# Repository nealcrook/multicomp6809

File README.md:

---
DOCUMENTATION: For instructions and other documentation for these files, refer to the Wiki (use the link at the top of the page). You might not see the link if you are using a mobile device -- you may need to select "desktop version"
---

I always wanted a 6809 machine. I still have the A4 notebook where I sketched out design ideas. However, I never simultaneously had the time and money to build one from scratch (even though I have accumulated all of the parts in my junk box over the years).

When I saw this http://searle.hostei.com/grant/Multicomp/index.html I realised I could satisfy my yearning without too much soldering.

I decided that I would run Brad Rodriguez's Camelforth on it. Before I did that I resussitated a 6809 emulator and added crude support first for Brad's "scroungmaster" machine and then for the 6809 multicomp machine. That emulator is https://github.com/nealcrook/exec09.

Camelforth is currently running on real hardware. Using a hardware bank-switching unit on multicomp Camelforth can also act as boot loader for Grant's port of Microsoft ROM BASIC and for the N8VEM port of Dave Dunfield's CUBIX and for my ports of FLEX, NitrOS-9, BUGGY and FUZIX. All of this also runs on exec09.

This repository is a venue for sharing the hardware and software that I have used on my multicomp.

For detail on how to use any of this stuff, click on the "wiki" button on the right.

More on CamelForth here:
https://launchpad.net/camelforth
http://www.camelforth.com/
http://www.bradrodriguez.com/papers/index.html

Approximate WIKI Change Log:

03Feb2016 Rework FLEX stuff to add more detail and make it clearer

05Feb2016 Rework CUBIX stuff to describe new single-step boot. Remove references to obsolete SDINIT.

12Feb2016 New BUGGY source code - single step now works. Expanded WIKI pages on CamelForth to add some links on tutorials. New versions of TERMINAL and UART VHDL to add functional reset of input FIFOs to avoid some start-up problems.

09Aug2018 Tidy-up pass - adding a few misisng files and scripts and generally tidying things up. In particular, clean up the build process for the 6809 ROM BASIC and add some images for simulation debug.

06Mar2019 Reorganisation to try to provided consistent descriptions for each operating environment: the original material  evolved over time as I ported successive bits of code and it shows (too much) in places.

24May2020 WIKI was a mix of creole and markdown. I am gradually migrating all the pages to markdown, making various small updates on the way. Expand the pages on camelforth to describe how to build it at a different start address.

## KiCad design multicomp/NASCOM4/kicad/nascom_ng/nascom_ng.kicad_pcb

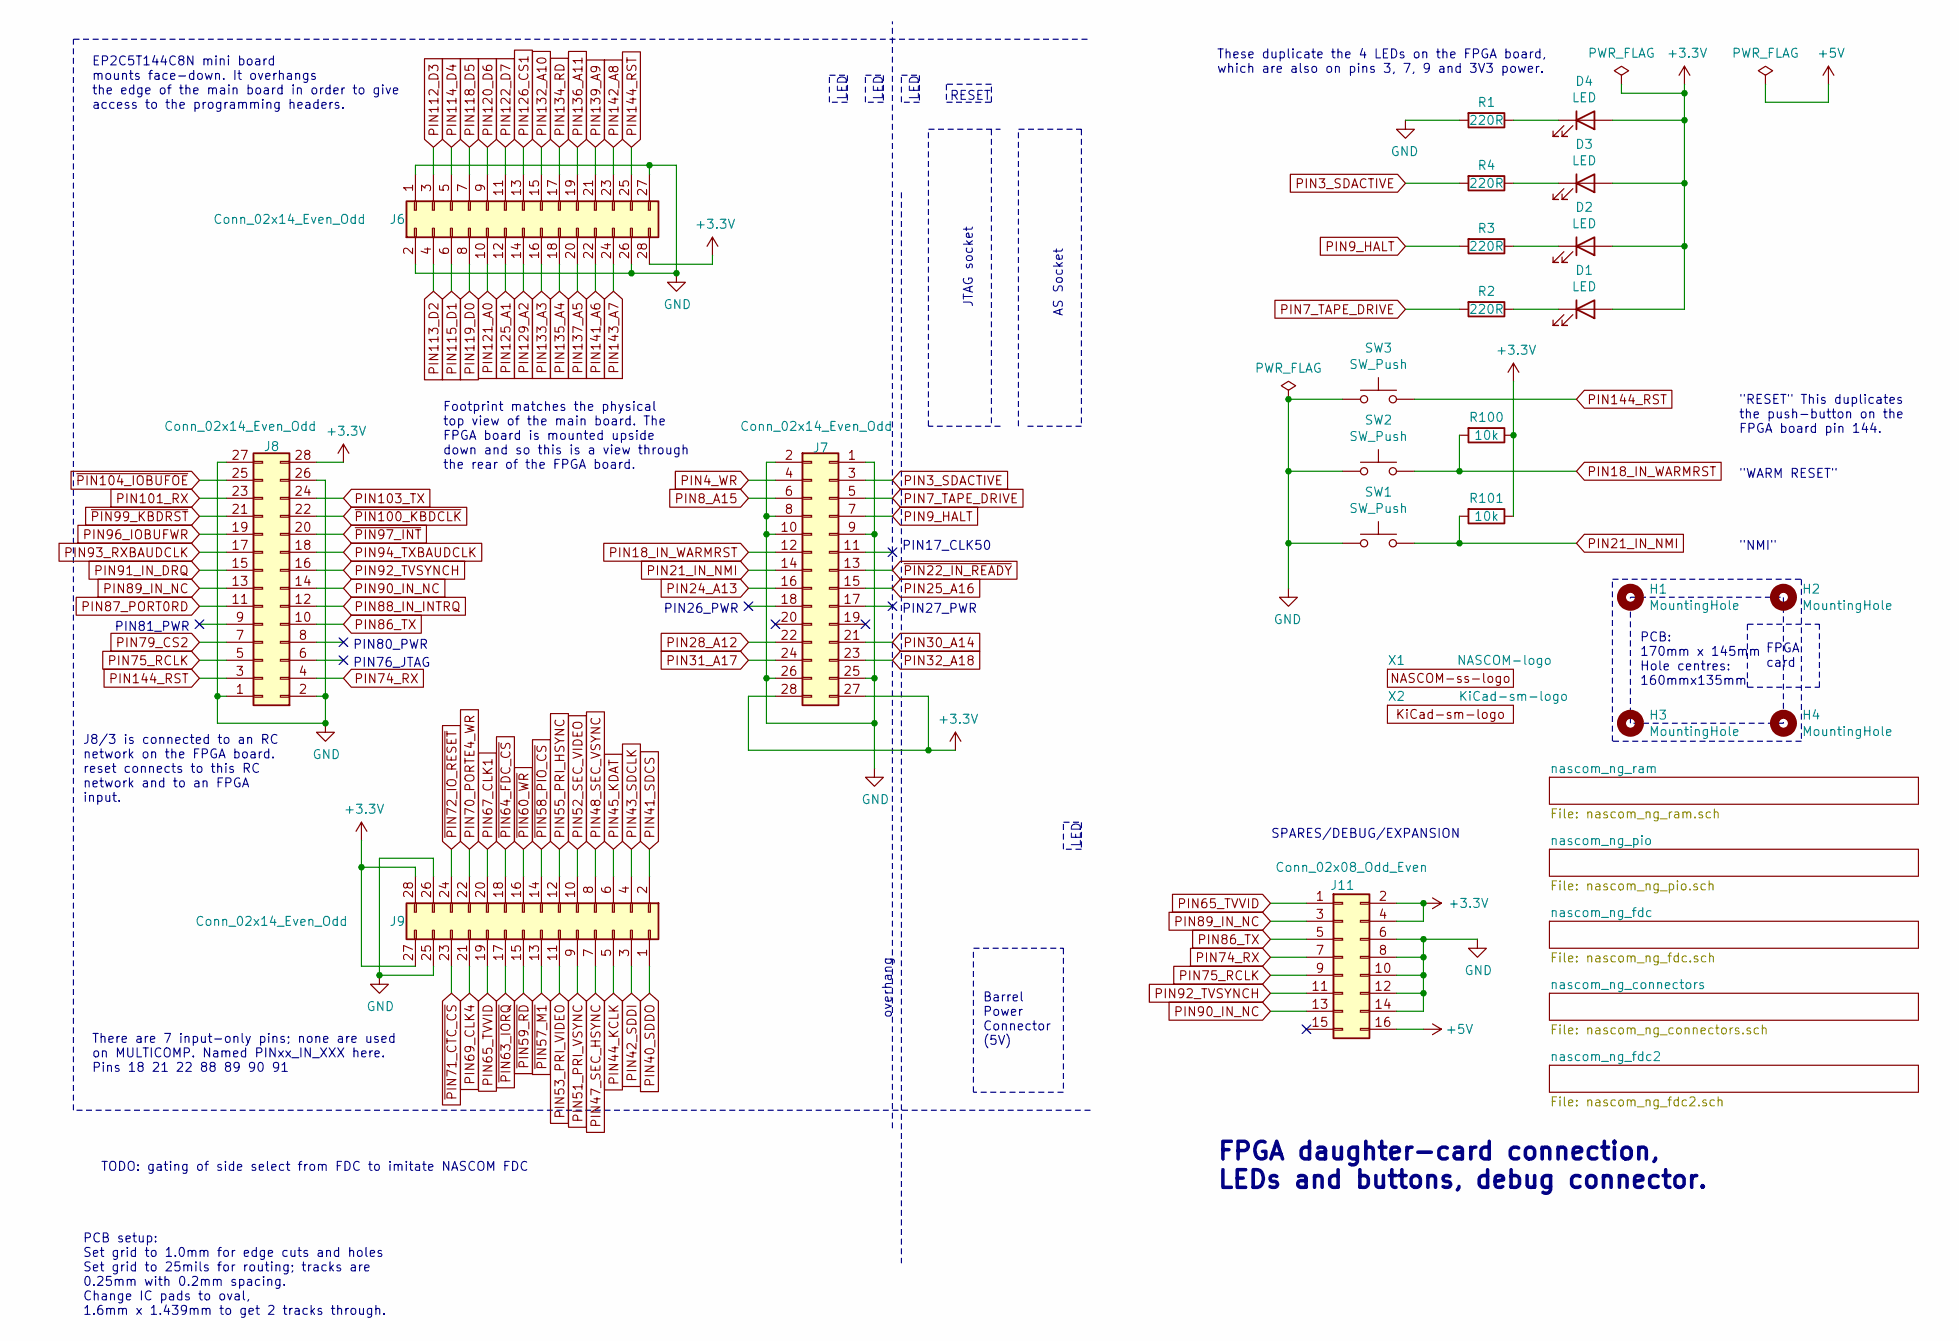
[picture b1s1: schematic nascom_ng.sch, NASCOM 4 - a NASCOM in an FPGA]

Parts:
D1, D2, D3, D4: LED; LED_D5.0mm
H1, H2, H3, H4: MountingHole; MountingHole_3.2mm_M3
J6, J7, J8, J9: Conn_02x14_Even_Odd; PinSocket_2x14_P2.54mm_Vertical
J11: Conn_02x08_Odd_Even; IDC-Header_2x08_P2.54mm_Vertical
R1, R2, R3, R4: 220R; R_Axial_DIN0204_L3.6mm_D1.6mm_P7.62mm_Horizontal
R100, R101: 10k; R_Axial_DIN0204_L3.6mm_D1.6mm_P7.62mm_Horizontal
SW1, SW2, SW3: SW_Push; MOMENTARY_TACTILE_RT_ANGLE
X1: NASCOM-logo; nascom_logo_tiny
X2: KiCad-sm-logo; KiCad-Logo_5mm_SolderMask

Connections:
+5V: J11.16; also elsewhere on the board
GND: J6.1, J6.2, J6.26, J6.27, J7.1, J7.2, J7.8, J7.9, J7.10, J7.25, J7.26, J8.1, J8.2, J8.26, J8.27, J9.25, J9.26, J11.6, J11.8, J11.10, J11.12, J11.14, R1.2, SW1.1, SW2.1, SW3.1; also elsewhere on the board
unnamed: D1.1 (K), R2.1
unnamed: D2.1 (K), R3.1
unnamed: D3.1 (K), R4.1
unnamed: D4.1 (K), R1.1
PIN3_SDACTIVE: J7.3, R4.2
PIN4_WR: J7.4; also elsewhere on the board
PIN7_TAPE_DRIVE: J7.5, R2.2; also elsewhere on the board
PIN8_A15: J7.6; also elsewhere on the board
PIN9_HALT: J7.7, R3.2
PIN18_IN_WARMRST: J7.12, R100.2, SW2.2
PIN21_IN_NMI: J7.14, R101.2, SW1.2; also elsewhere on the board
PIN24_A13: J7.16; also elsewhere on the board
PIN25_A16: J7.15; also elsewhere on the board
PIN28_A12: J7.22; also elsewhere on the board
PIN30_A14: J7.21; also elsewhere on the board
PIN31_A17: J7.24; also elsewhere on the board
PIN32_A18: J7.23; also elsewhere on the board
PIN40_SDDO: J9.1; also elsewhere on the board
PIN41_SDCS: J9.2; also elsewhere on the board
PIN42_SDDI: J9.3; also elsewhere on the board
PIN43_SDCLK: J9.4; also elsewhere on the board
PIN44_KCLK: J9.5; also elsewhere on the board
PIN45_KDAT: J9.6; also elsewhere on the board
PIN47_SEC_HSYNC: J9.7; also elsewhere on the board
PIN48_SEC_VSYNC: J9.8; also elsewhere on the board
PIN51_PRI_VSYNC: J9.9; also elsewhere on the board
PIN52_SEC_VIDEO: J9.10; also elsewhere on the board
PIN53_PRI_VIDEO: J9.11; also elsewhere on the board
PIN55_PRI_HSYNC: J9.12; also elsewhere on the board
PIN65_TVVID: J9.19, J11.1
PIN67_CLK1: J9.20; also elsewhere on the board
PIN69_CLK4: J9.21; also elsewhere on the board
PIN70_PORTE4_WR: J9.22; also elsewhere on the board
PIN74_RX: J8.4, J11.7
PIN75_RCLK: J8.5, J11.9
PIN79_CS2: J8.7; also elsewhere on the board
PIN86_TX: J8.10, J11.5
PIN87_PORT0RD: J8.11; also elsewhere on the board
PIN88_IN_INTRQ: J8.12; also elsewhere on the board
PIN89_IN_NC: J8.13, J11.3
PIN90_IN_NC: J8.14, J11.13
PIN91_IN_DRQ: J8.15; also elsewhere on the board
PIN92_TVSYNCH: J8.16, J11.11
PIN93_RXBAUDCLK: J8.17; also elsewhere on the board
PIN94_TXBAUDCLK: J8.18; also elsewhere on the board
PIN96_IOBUFWR: J8.19; also elsewhere on the board
PIN101_RX: J8.23; also elsewhere on the board
PIN103_TX: J8.24; also elsewhere on the board
PIN112_D3: J6.3; also elsewhere on the board
PIN113_D2: J6.4; also elsewhere on the board
PIN114_D4: J6.5; also elsewhere on the board
PIN115_D1: J6.6; also elsewhere on the board
PIN118_D5: J6.7; also elsewhere on the board
PIN119_D0: J6.8; also elsewhere on the board
PIN120_D6: J6.9; also elsewhere on the board
PIN121_A0: J6.10; also elsewhere on the board
PIN122_D7: J6.11; also elsewhere on the board
PIN125_A1: J6.12; also elsewhere on the board
PIN126_CS1: J6.13; also elsewhere on the board
PIN129_A2: J6.14; also elsewhere on the board
PIN132_A10: J6.15; also elsewhere on the board
PIN133_A3: J6.16; also elsewhere on the board
PIN134_RD: J6.17; also elsewhere on the board
PIN135_A4: J6.18; also elsewhere on the board
PIN136_A11: J6.19; also elsewhere on the board
PIN137_A5: J6.20; also elsewhere on the board
PIN139_A9: J6.21; also elsewhere on the board
PIN141_A6: J6.22; also elsewhere on the board
PIN142_A8: J6.23; also elsewhere on the board
PIN143_A7: J6.24; also elsewhere on the board
PIN144_RST: J6.25, J8.3, SW3.2; also elsewhere on the board
~PIN22_IN_READY: J7.13; also elsewhere on the board
~PIN57_M1: J9.13; also elsewhere on the board
~PIN58_PIO_CS: J9.14; also elsewhere on the board
~PIN59_RD: J9.15; also elsewhere on the board
~PIN60_WR: J9.16; also elsewhere on the board
~PIN63_IORQ: J9.17; also elsewhere on the board
~PIN64_FDC_CS: J9.18; also elsewhere on the board
~PIN71_CTC_CS: J9.23; also elsewhere on the board
~PIN72_IO_RESET: J9.24; also elsewhere on the board
~PIN97_INT: J8.20; also elsewhere on the board
~PIN99_KBDRST: J8.21; also elsewhere on the board
~PIN100_KBDCLK: J8.22; also elsewhere on the board
~PIN104_IOBUFOE: J8.25; also elsewhere on the board

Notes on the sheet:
Footprint matches the physical top view of the main board. The FPGA board is mounted upside down and so this is a view through the rear of the FPGA board.
AS Socket
JTAG socket
Barrel Power Connector (5V)
There are 7 input-only pins; none are used on MULTICOMP. Named PINxx_IN_XXX here. Pins 18 21 22 88 89 90 91
"RESET" This duplicates the push-button on the FPGA board pin 144.
TODO: gating of side select from FDC to imitate NASCOM FDC
PIN17_CLK50
PIN27_PWR
PIN26_PWR
PIN81_PWR
PIN76_JTAG
PIN80_PWR
These duplicate the 4 LEDs on the FPGA board, which are also on pins 3, 7, 9 and 3V3 power.
J8/3 is connected to an RC network on the FPGA board. reset connects to this RC network and to an FPGA input.
EP2C5T144C8N mini board mounts face-down. It overhangs the edge of the main board in order to give access to the programming headers.
RESET
LED
overhang
"NMI"
"WARM RESET"
SPARES/DEBUG/EXPANSION
FPGA daughter-card connection, LEDs and buttons, debug connector.
PCB: 170mm x 145mm Hole centres: 160mmx135mm
FPGA card
PCB setup: Set grid to 1.0mm for edge cuts and holes Set grid to 25mils for routing; tracks are 0.25mm with 0.2mm spacing. Change IC pads to oval, 1.6mm x 1.439mm to get 2 tracks through.

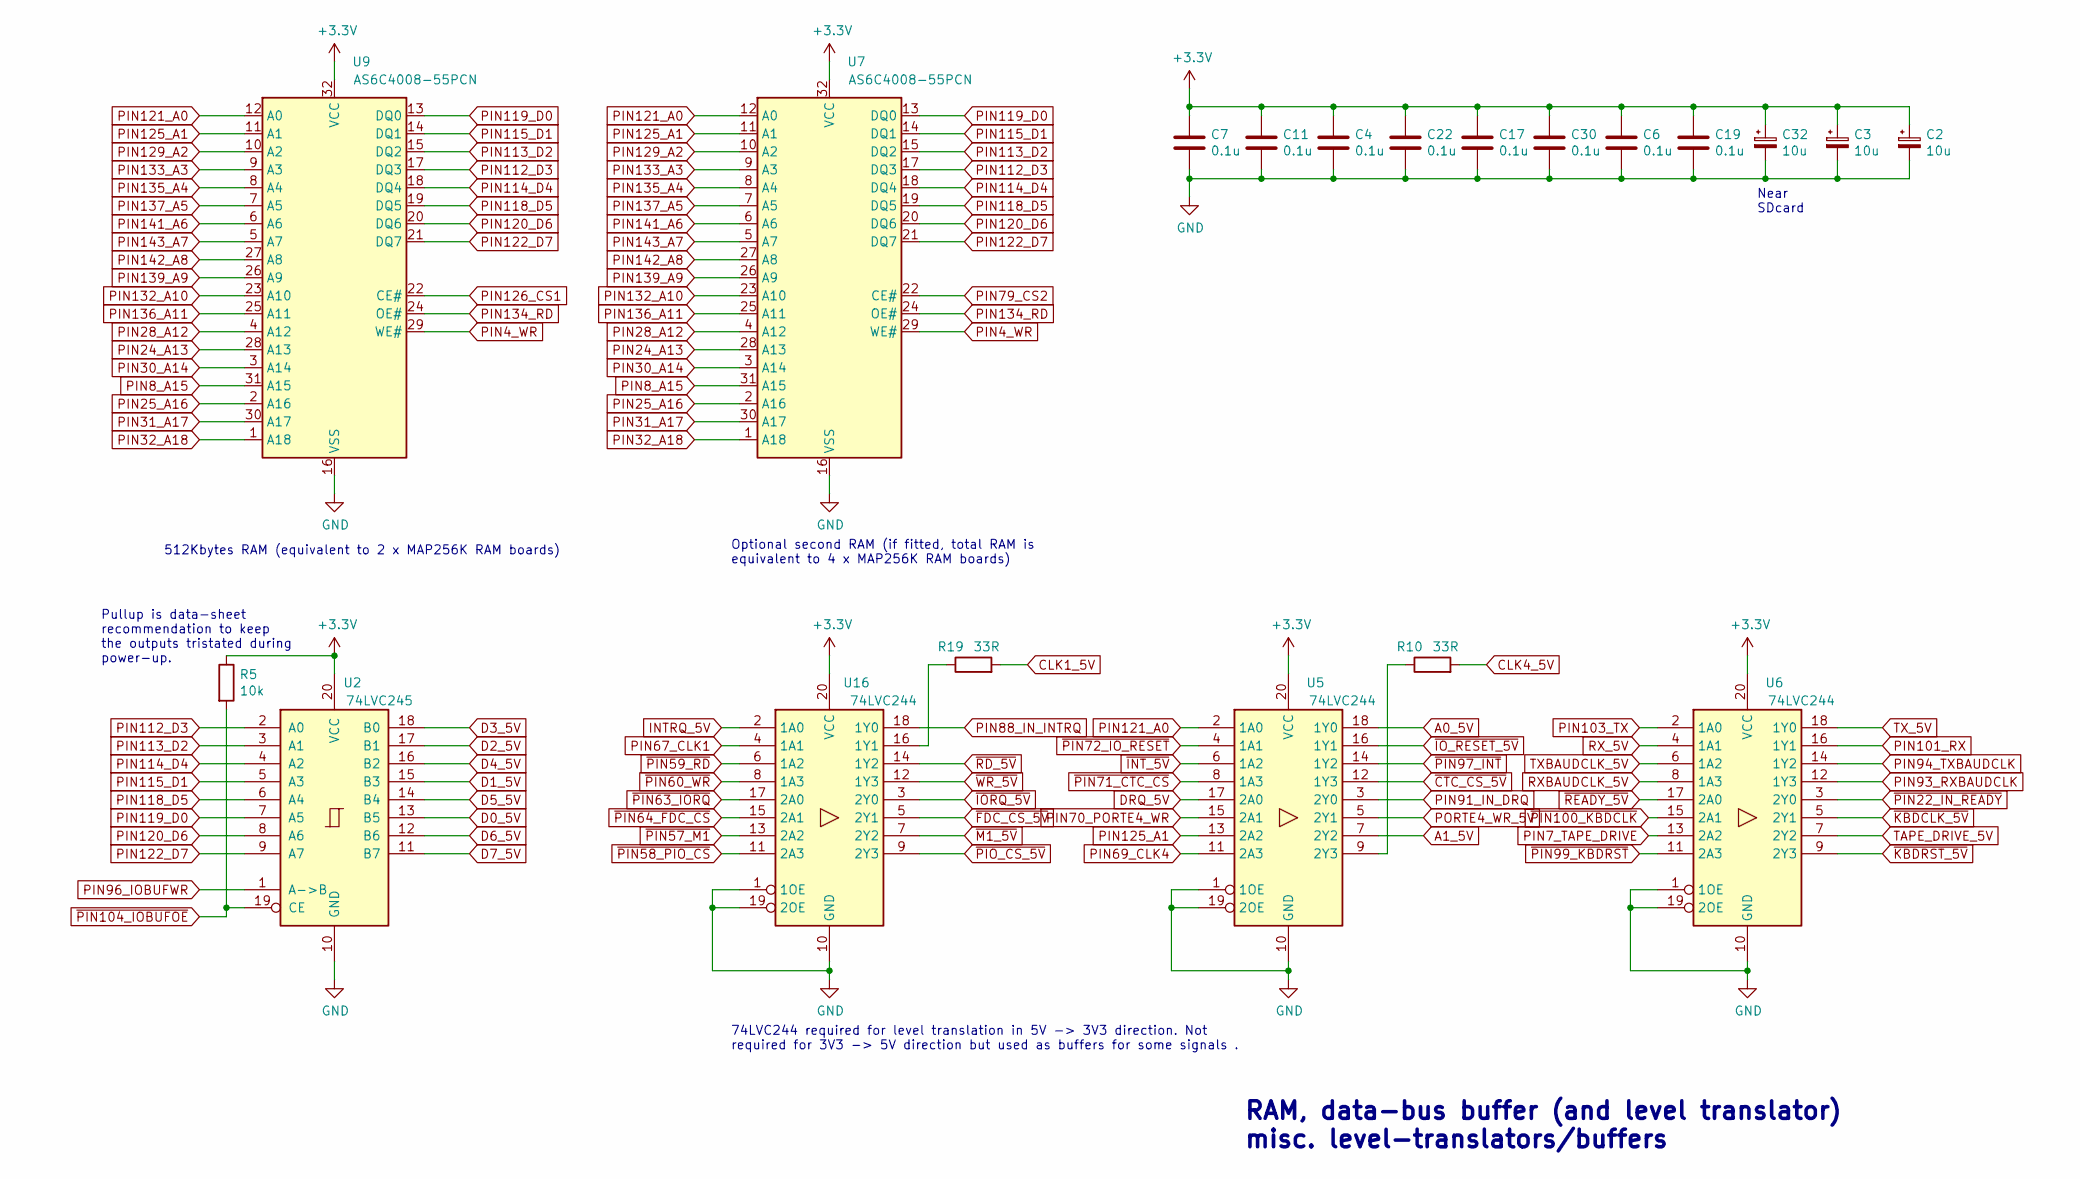
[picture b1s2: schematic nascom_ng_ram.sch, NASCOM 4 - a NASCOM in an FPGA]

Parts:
C2, C3, C32: 10u; CP_Radial_D5.0mm_P2.50mm
C4, C6, C7, C11, C17, C19, C22, C30: 0.1u; C_Disc_D3.0mm_W2.0mm_P2.50mm
R5: 10k; R_Axial_DIN0204_L3.6mm_D1.6mm_P7.62mm_Horizontal
R10, R19: 33R; R_Axial_DIN0204_L3.6mm_D1.6mm_P7.62mm_Horizontal
U2: 74LVC245; DIP-20_W7.62mm
U5, U6, U16: 74LVC244; DIP-20_W7.62mm
U7, U9: AS6C4008-55PCN; DIP-32_W15.24mm

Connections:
A0_5V: U5.18 (1Y0); also elsewhere on the board
A1_5V: U5.7 (2Y2); also elsewhere on the board
CLK1_5V: R19.2; also elsewhere on the board
CLK4_5V: R10.2; also elsewhere on the board
D0_5V: U2.13 (B5); also elsewhere on the board
D1_5V: U2.15 (B3); also elsewhere on the board
D2_5V: U2.17 (B1); also elsewhere on the board
D3_5V: U2.18 (B0); also elsewhere on the board
D4_5V: U2.16 (B2); also elsewhere on the board
D5_5V: U2.14 (B4); also elsewhere on the board
D6_5V: U2.12 (B6); also elsewhere on the board
D7_5V: U2.11 (B7); also elsewhere on the board
DRQ_5V: U5.17 (2A0); also elsewhere on the board
GND: C2.2, C3.2, C4.2, C6.2, C7.2, C11.2, C17.2, C19.2, C22.2, C30.2, C32.2, U2.10 (GND), U5.1 (1OE), U5.10 (GND), U5.19 (2OE), U6.1 (1OE), U6.10 (GND), U6.19 (2OE), U7.16 (VSS), U9.16 (VSS), U16.1 (1OE), U16.10 (GND), U16.19 (2OE); also elsewhere on the board
INTRQ_5V: U16.2 (1A0); also elsewhere on the board
unnamed: R10.1, U5.9 (2Y3)
unnamed: R19.1, U16.16 (1Y1)
PIN4_WR: U7.29 (WE#), U9.29 (WE#); also elsewhere on the board
PIN7_TAPE_DRIVE: U6.13 (2A2); also elsewhere on the board
PIN8_A15: U7.31 (A15), U9.31 (A15); also elsewhere on the board
PIN24_A13: U7.28 (A13), U9.28 (A13); also elsewhere on the board
PIN25_A16: U7.2 (A16), U9.2 (A16); also elsewhere on the board
PIN28_A12: U7.4 (A12), U9.4 (A12); also elsewhere on the board
PIN30_A14: U7.3 (A14), U9.3 (A14); also elsewhere on the board
PIN31_A17: U7.30 (A17), U9.30 (A17); also elsewhere on the board
PIN32_A18: U7.1 (A18), U9.1 (A18); also elsewhere on the board
PIN67_CLK1: U16.4 (1A1); also elsewhere on the board
PIN69_CLK4: U5.11 (2A3); also elsewhere on the board
PIN70_PORTE4_WR: U5.15 (2A1); also elsewhere on the board
PIN79_CS2: U7.22 (CE#); also elsewhere on the board
PIN88_IN_INTRQ: U16.18 (1Y0); also elsewhere on the board
PIN91_IN_DRQ: U5.3 (2Y0); also elsewhere on the board
PIN93_RXBAUDCLK: U6.12 (1Y3); also elsewhere on the board
PIN94_TXBAUDCLK: U6.14 (1Y2); also elsewhere on the board
PIN96_IOBUFWR: U2.1 (A->B); also elsewhere on the board
PIN101_RX: U6.16 (1Y1); also elsewhere on the board
PIN103_TX: U6.2 (1A0); also elsewhere on the board
PIN112_D3: U2.2 (A0), U7.17 (DQ3), U9.17 (DQ3); also elsewhere on the board
PIN113_D2: U2.3 (A1), U7.15 (DQ2), U9.15 (DQ2); also elsewhere on the board
PIN114_D4: U2.4 (A2), U7.18 (DQ4), U9.18 (DQ4); also elsewhere on the board
PIN115_D1: U2.5 (A3), U7.14 (DQ1), U9.14 (DQ1); also elsewhere on the board
PIN118_D5: U2.6 (A4), U7.19 (DQ5), U9.19 (DQ5); also elsewhere on the board
PIN119_D0: U2.7 (A5), U7.13 (DQ0), U9.13 (DQ0); also elsewhere on the board
PIN120_D6: U2.8 (A6), U7.20 (DQ6), U9.20 (DQ6); also elsewhere on the board
PIN121_A0: U5.2 (1A0), U7.12 (A0), U9.12 (A0); also elsewhere on the board
PIN122_D7: U2.9 (A7), U7.21 (DQ7), U9.21 (DQ7); also elsewhere on the board
PIN125_A1: U5.13 (2A2), U7.11 (A1), U9.11 (A1); also elsewhere on the board
PIN126_CS1: U9.22 (CE#); also elsewhere on the board
PIN129_A2: U7.10 (A2), U9.10 (A2); also elsewhere on the board
PIN132_A10: U7.23 (A10), U9.23 (A10); also elsewhere on the board
PIN133_A3: U7.9 (A3), U9.9 (A3); also elsewhere on the board
PIN134_RD: U7.24 (OE#), U9.24 (OE#); also elsewhere on the board
PIN135_A4: U7.8 (A4), U9.8 (A4); also elsewhere on the board
PIN136_A11: U7.25 (A11), U9.25 (A11); also elsewhere on the board
PIN137_A5: U7.7 (A5), U9.7 (A5); also elsewhere on the board
PIN139_A9: U7.26 (A9), U9.26 (A9); also elsewhere on the board
PIN141_A6: U7.6 (A6), U9.6 (A6); also elsewhere on the board
PIN142_A8: U7.27 (A8), U9.27 (A8); also elsewhere on the board
PIN143_A7: U7.5 (A7), U9.5 (A7); also elsewhere on the board
PORTE4_WR_5V: U5.5 (2Y1); also elsewhere on the board
RXBAUDCLK_5V: U6.8 (1A3); also elsewhere on the board
RX_5V: U6.4 (1A1); also elsewhere on the board
TAPE_DRIVE_5V: U6.7 (2Y2); also elsewhere on the board
TXBAUDCLK_5V: U6.6 (1A2); also elsewhere on the board
TX_5V: U6.18 (1Y0); also elsewhere on the board
~CTC_CS_5V: U5.12 (1Y3); also elsewhere on the board
~FDC_CS_5V: U16.5 (2Y1); also elsewhere on the board
~INT_5V: U5.6 (1A2); also elsewhere on the board
~IORQ_5V: U16.3 (2Y0); also elsewhere on the board
~IO_RESET_5V: U5.16 (1Y1); also elsewhere on the board
~KBDCLK_5V: U6.5 (2Y1); also elsewhere on the board
~KBDRST_5V: U6.9 (2Y3); also elsewhere on the board
~M1_5V: U16.7 (2Y2); also elsewhere on the board
~PIN22_IN_READY: U6.3 (2Y0); also elsewhere on the board
~PIN57_M1: U16.13 (2A2); also elsewhere on the board
~PIN58_PIO_CS: U16.11 (2A3); also elsewhere on the board
~PIN59_RD: U16.6 (1A2); also elsewhere on the board
~PIN60_WR: U16.8 (1A3); also elsewhere on the board
~PIN63_IORQ: U16.17 (2A0); also elsewhere on the board
~PIN64_FDC_CS: U16.15 (2A1); also elsewhere on the board
~PIN71_CTC_CS: U5.8 (1A3); also elsewhere on the board
~PIN72_IO_RESET: U5.4 (1A1); also elsewhere on the board
~PIN97_INT: U5.14 (1Y2); also elsewhere on the board
~PIN99_KBDRST: U6.11 (2A3); also elsewhere on the board
~PIN100_KBDCLK: U6.15 (2A1); also elsewhere on the board
~PIN104_IOBUFOE: R5.2, U2.19 (CE); also elsewhere on the board
~PIO_CS_5V: U16.9 (2Y3); also elsewhere on the board
~RD_5V: U16.14 (1Y2); also elsewhere on the board
~READY_5V: U6.17 (2A0); also elsewhere on the board
~WR_5V: U16.12 (1Y3); also elsewhere on the board

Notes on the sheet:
512Kbytes RAM (equivalent to 2 x MAP256K RAM boards)
Optional second RAM (if fitted, total RAM is equivalent to 4 x MAP256K RAM boards)
Pullup is data-sheet recommendation to keep the outputs tristated during power-up.
74LVC244 required for level translation in 5V -> 3V3 direction. Not required for 3V3 -> 5V direction but used as buffers for some signals .
RAM, data-bus buffer (and level translator) misc. level-translators/buffers
Near SDcard

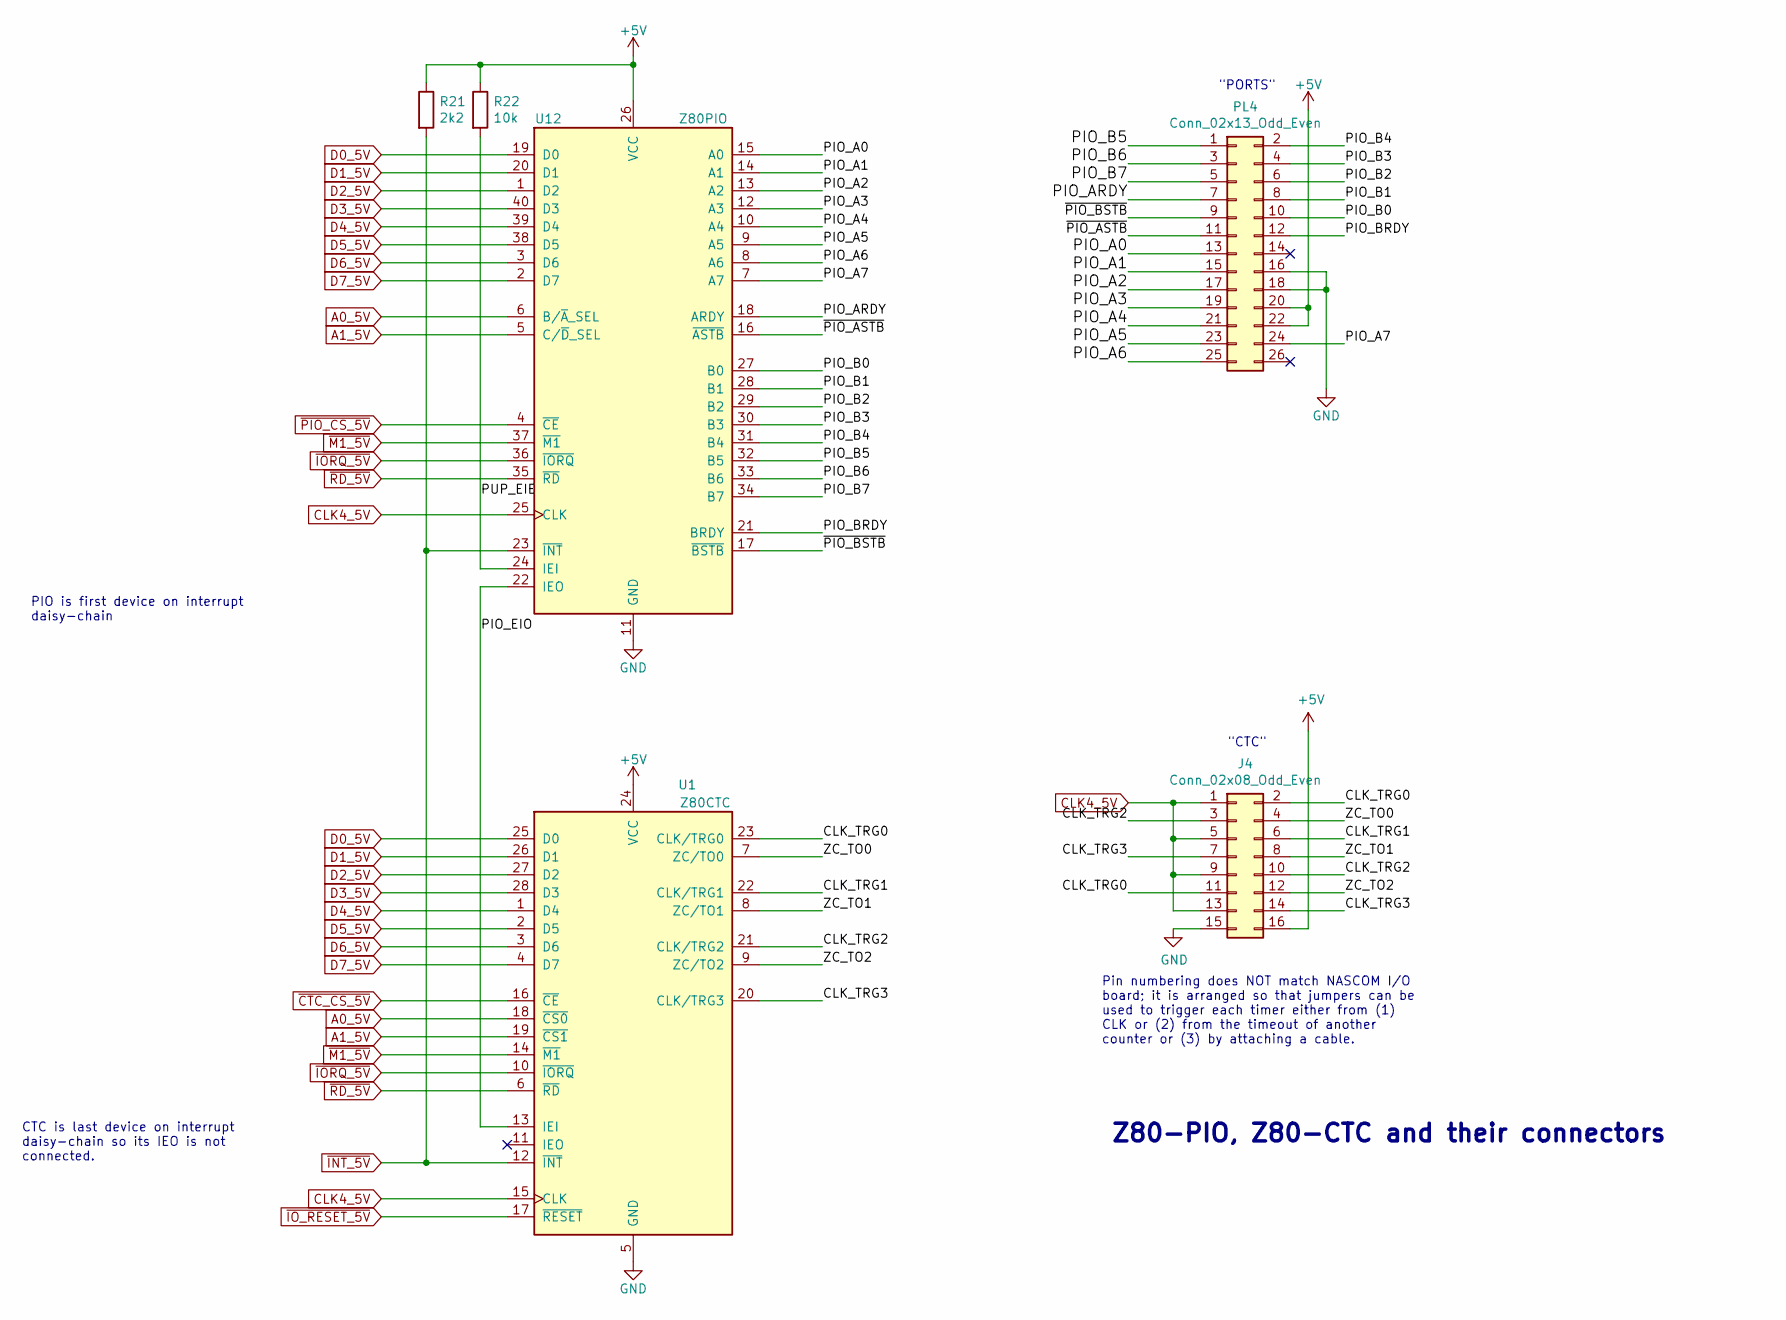
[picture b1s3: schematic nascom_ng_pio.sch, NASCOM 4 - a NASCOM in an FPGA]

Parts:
J4: Conn_02x08_Odd_Even; IDC-Header_2x08_P2.54mm_Vertical
PL4: Conn_02x13_Odd_Even; IDC-Header_2x13_P2.54mm_Vertical
R21: 2k2; R_Axial_DIN0204_L3.6mm_D1.6mm_P7.62mm_Horizontal
R22: 10k; R_Axial_DIN0204_L3.6mm_D1.6mm_P7.62mm_Horizontal
U1: Z80CTC; DIP-28_W15.24mm
U12: Z80PIO; DIP-40_W15.24mm

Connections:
+5V: J4.16, PL4.20, PL4.22, R21.1, R22.1, U1.24 (VCC), U12.26 (VCC); also elsewhere on the board
/nascom_ng_pio/CLK_TRG0: J4.2, J4.11, U1.23 (CLK/TRG0)
/nascom_ng_pio/CLK_TRG1: J4.6, U1.22 (CLK/TRG1)
/nascom_ng_pio/CLK_TRG2: J4.3, J4.10, U1.21 (CLK/TRG2)
/nascom_ng_pio/CLK_TRG3: J4.7, J4.14, U1.20 (CLK/TRG3)
/nascom_ng_pio/PIO_A0: PL4.13, U12.15 (A0)
/nascom_ng_pio/PIO_A1: PL4.15, U12.14 (A1)
/nascom_ng_pio/PIO_A2: PL4.17, U12.13 (A2)
/nascom_ng_pio/PIO_A3: PL4.19, U12.12 (A3)
/nascom_ng_pio/PIO_A4: PL4.21, U12.10 (A4)
/nascom_ng_pio/PIO_A5: PL4.23, U12.9 (A5)
/nascom_ng_pio/PIO_A6: PL4.25, U12.8 (A6)
/nascom_ng_pio/PIO_A7: PL4.24, U12.7 (A7)
/nascom_ng_pio/PIO_ARDY: PL4.7, U12.18 (ARDY)
/nascom_ng_pio/PIO_B0: PL4.10, U12.27 (B0)
/nascom_ng_pio/PIO_B1: PL4.8, U12.28 (B1)
/nascom_ng_pio/PIO_B2: PL4.6, U12.29 (B2)
/nascom_ng_pio/PIO_B3: PL4.4, U12.30 (B3)
/nascom_ng_pio/PIO_B4: PL4.2, U12.31 (B4)
/nascom_ng_pio/PIO_B5: PL4.1, U12.32 (B5)
/nascom_ng_pio/PIO_B6: PL4.3, U12.33 (B6)
/nascom_ng_pio/PIO_B7: PL4.5, U12.34 (B7)
/nascom_ng_pio/PIO_BRDY: PL4.12, U12.21 (BRDY)
/nascom_ng_pio/PIO_EIO: U1.13 (IEI), U12.22 (IEO)
/nascom_ng_pio/PUP_EIE: R22.2, U12.24 (IEI)
/nascom_ng_pio/ZC_TO0: J4.4, U1.7 (ZC/TO0)
/nascom_ng_pio/ZC_TO1: J4.8, U1.8 (ZC/TO1)
/nascom_ng_pio/ZC_TO2: J4.12, U1.9 (ZC/TO2)
/nascom_ng_pio/~PIO_ASTB: PL4.11, U12.16 (~ASTB~)
/nascom_ng_pio/~PIO_BSTB: PL4.9, U12.17 (~BSTB~)
A0_5V: U1.18 (~CS0), U12.6 (B/~A~_SEL); also elsewhere on the board
A1_5V: U1.19 (~CS1), U12.5 (C/~D~_SEL); also elsewhere on the board
CLK4_5V: J4.1, J4.5, J4.9, J4.13, U1.15 (CLK), U12.25 (CLK); also elsewhere on the board
D0_5V: U1.25 (D0), U12.19 (D0); also elsewhere on the board
D1_5V: U1.26 (D1), U12.20 (D1); also elsewhere on the board
D2_5V: U1.27 (D2), U12.1 (D2); also elsewhere on the board
D3_5V: U1.28 (D3), U12.40 (D3); also elsewhere on the board
D4_5V: U1.1 (D4), U12.39 (D4); also elsewhere on the board
D5_5V: U1.2 (D5), U12.38 (D5); also elsewhere on the board
D6_5V: U1.3 (D6), U12.3 (D6); also elsewhere on the board
D7_5V: U1.4 (D7), U12.2 (D7); also elsewhere on the board
GND: J4.15, PL4.16, PL4.18, U1.5 (GND), U12.11 (GND); also elsewhere on the board
~CTC_CS_5V: U1.16 (~CE~); also elsewhere on the board
~INT_5V: R21.2, U1.12 (~INT~), U12.23 (~INT~); also elsewhere on the board
~IORQ_5V: U1.10 (~IORQ~), U12.36 (~IORQ~); also elsewhere on the board
~IO_RESET_5V: U1.17 (~RESET); also elsewhere on the board
~M1_5V: U1.14 (~M1~), U12.37 (~M1~); also elsewhere on the board
~PIO_CS_5V: U12.4 (~CE~); also elsewhere on the board
~RD_5V: U1.6 (~RD~), U12.35 (~RD~); also elsewhere on the board

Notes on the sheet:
PIO is first device on interrupt daisy-chain
Pin numbering does NOT match NASCOM I/O board; it is arranged so that jumpers can be used to trigger each timer either from (1) CLK or (2) from the timeout of another counter or (3) by attaching a cable.
"CTC"
CTC is last device on interrupt daisy-chain so its IEO is not connected.
Z80-PIO, Z80-CTC and their connectors
"PORTS"

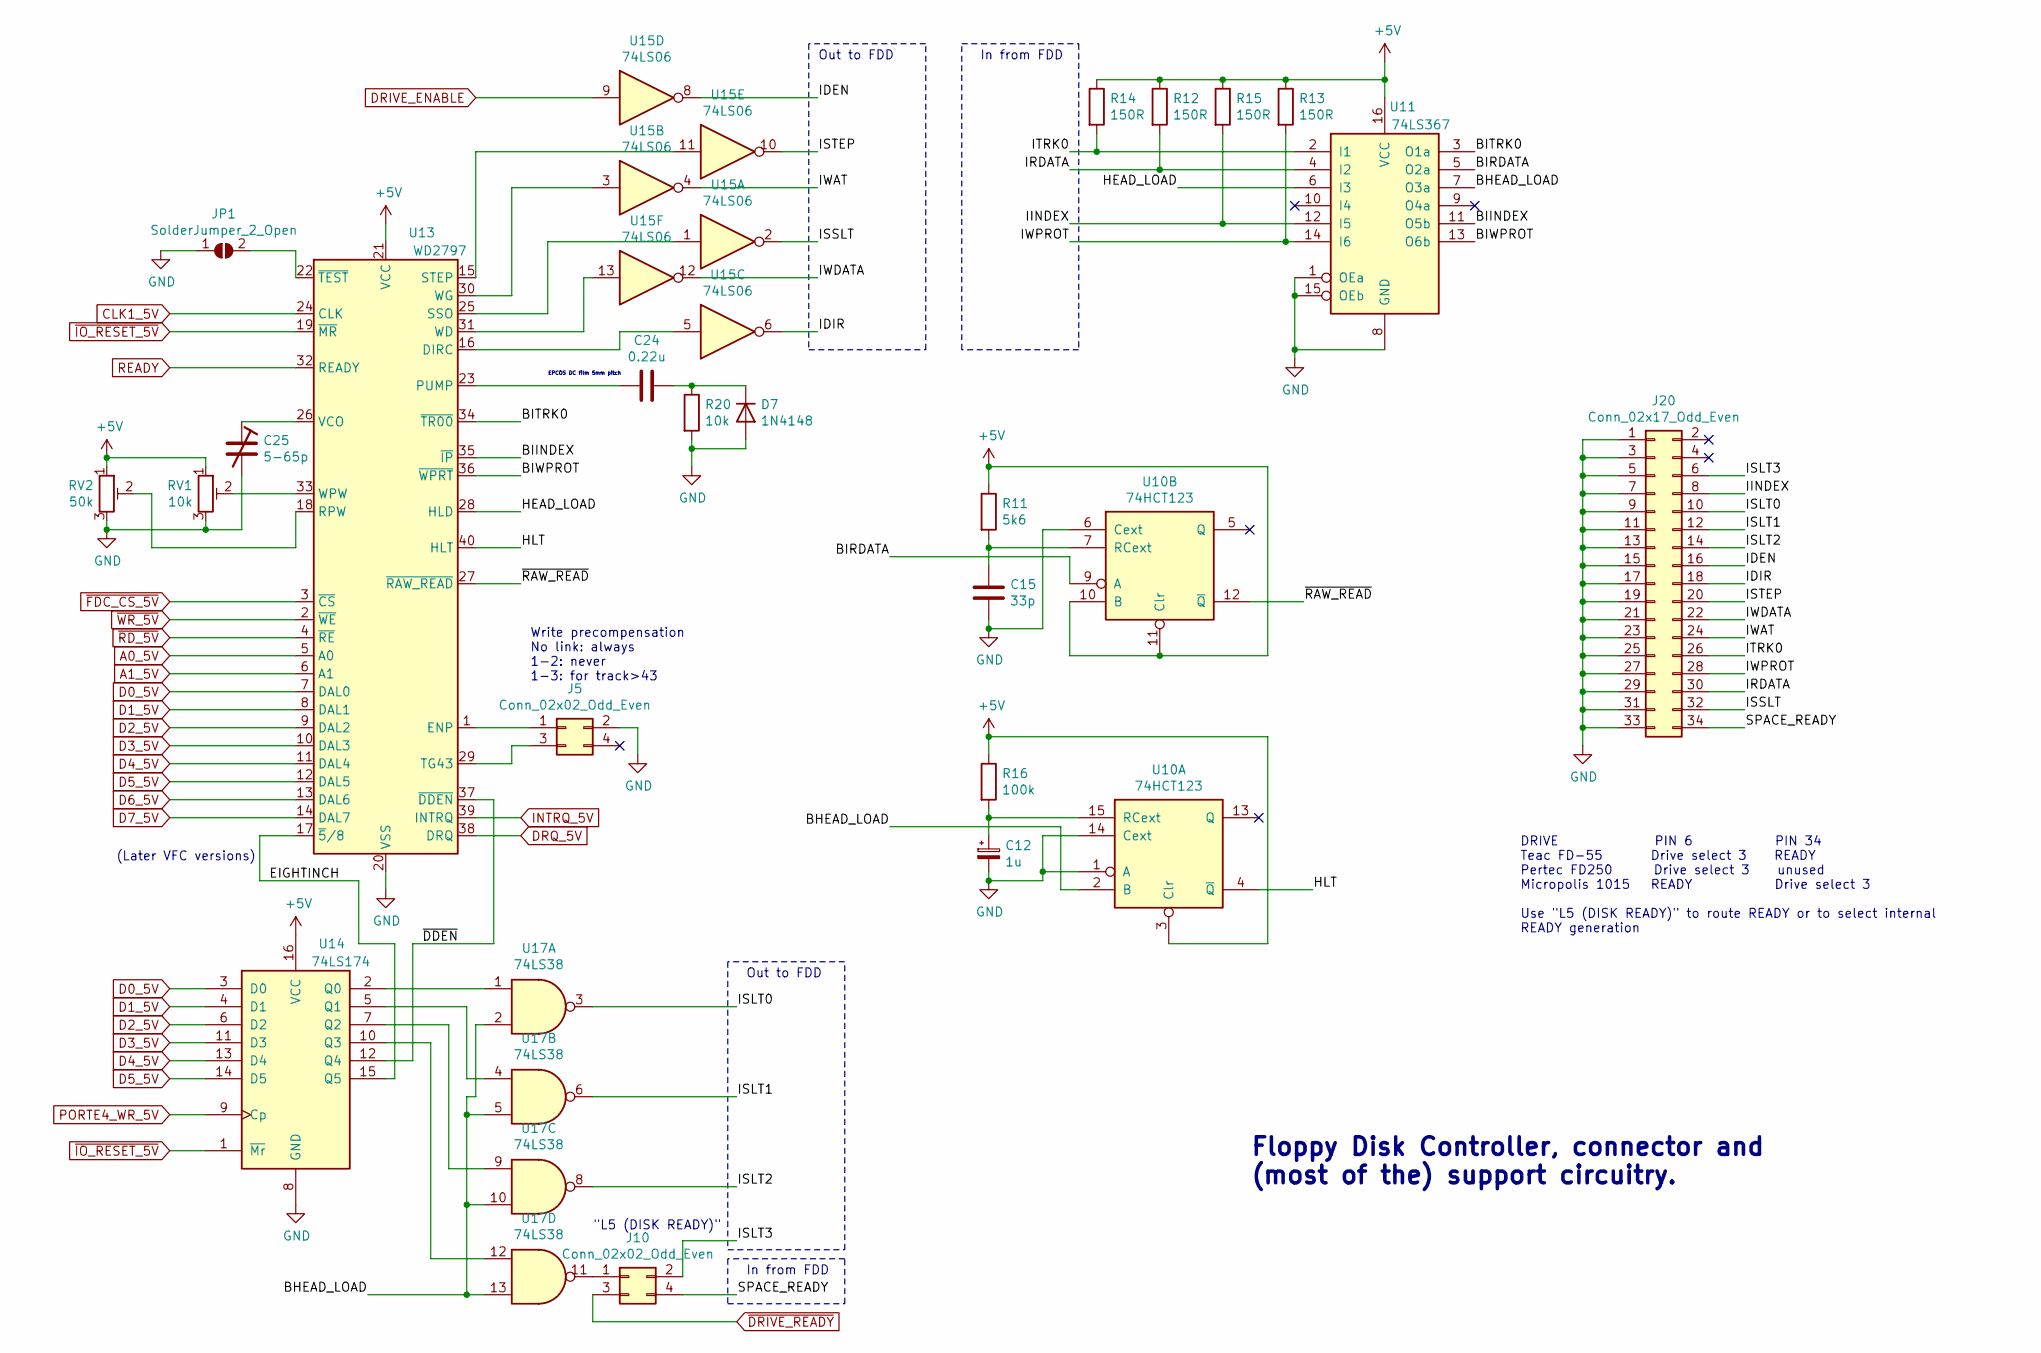
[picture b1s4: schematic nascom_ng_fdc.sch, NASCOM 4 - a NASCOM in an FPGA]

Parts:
C12: 1u; CP_Radial_Tantal_D4.5mm_P5.00mm
C15: 33p; C_Disc_D3.0mm_W2.0mm_P2.50mm
C24: 0.22u; C_Disc_D7.5mm_W2.5mm_P5.00mm
C25: 5-65p; Trimmer_Vishay_BFC2808_Fig2
D7: 1N4148; D_DO-35_SOD27_P7.62mm_Horizontal
J5, J10: Conn_02x02_Odd_Even; PinHeader_2x02_P2.54mm_Vertical
J20: Conn_02x17_Odd_Even; IDC-Header_2x17_P2.54mm_Vertical
JP1: SolderJumper_2_Open; SolderJumper-2_P1.3mm_Open_TrianglePad1.0x1.5mm
R11: 5k6; R_Axial_DIN0204_L3.6mm_D1.6mm_P7.62mm_Horizontal
R12, R13, R14, R15: 150R; R_Axial_DIN0204_L3.6mm_D1.6mm_P7.62mm_Horizontal
R16: 100k; R_Axial_DIN0204_L3.6mm_D1.6mm_P7.62mm_Horizontal
R20: 10k; R_Axial_DIN0204_L3.6mm_D1.6mm_P7.62mm_Horizontal
RV1: 10k; Potentiometer_Bourns_3296W_Vertical
RV2: 50k; Potentiometer_Bourns_3296W_Vertical
U10: 74HCT123; DIP-16_W7.62mm
U11: 74LS367; DIP-16_W7.62mm
U13: WD2797; DIP-40_W15.24mm
U14: 74LS174; DIP-16_W7.62mm
U15: 74LS06; DIP-14_W7.62mm
U17: 74LS38; DIP-14_W7.62mm

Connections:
+5V: R11.1, R12.1, R13.1, R14.1, R15.1, R16.1, RV1.1, RV2.1, U10.3 (Clr), U10.10 (B), U10.11 (Clr), U11.16 (VCC), U13.21 (VCC), U14.16 (VCC); also elsewhere on the board
/nascom_ng_fdc/BHEAD_LOAD: U10.2 (B), U11.7 (O3a), U17.2, U17.5, U17.10, U17.13
/nascom_ng_fdc/BIINDEX: U11.11 (O5b), U13.35 (~IP)
/nascom_ng_fdc/BIRDATA: U10.9 (A), U11.5 (O2a)
/nascom_ng_fdc/BITRK0: U11.3 (O1a), U13.34 (~TR00)
/nascom_ng_fdc/BIWPROT: U11.13 (O6b), U13.36 (~WPRT)
/nascom_ng_fdc/EIGHTINCH: U13.17 (~5~/8), U14.15 (Q5)
/nascom_ng_fdc/HEAD_LOAD: U11.6 (I3), U13.28 (HLD)
/nascom_ng_fdc/HLT: U10.4 (~Q), U13.40 (HLT)
/nascom_ng_fdc/IDEN: J20.16, U15.8
/nascom_ng_fdc/IDIR: J20.18, U15.6
/nascom_ng_fdc/IINDEX: J20.8, R15.2, U11.12 (I5)
/nascom_ng_fdc/IRDATA: J20.30, R12.2, U11.4 (I2)
/nascom_ng_fdc/ISLT0: J20.10, U17.3
/nascom_ng_fdc/ISLT1: J20.12, U17.6
/nascom_ng_fdc/ISLT2: J20.14, U17.8
/nascom_ng_fdc/ISLT3: J10.2, J20.6
/nascom_ng_fdc/ISSLT: J20.32, U15.2
/nascom_ng_fdc/ISTEP: J20.20, U15.10
/nascom_ng_fdc/ITRK0: J20.26, R14.2, U11.2 (I1)
/nascom_ng_fdc/IWAT: J20.24, U15.4
/nascom_ng_fdc/IWDATA: J20.22, U15.12
/nascom_ng_fdc/IWPROT: J20.28, R13.2, U11.14 (I6)
/nascom_ng_fdc/SPACE_READY: J10.4, J20.34
/nascom_ng_fdc/~DDEN: U13.37 (~DDEN), U14.12 (Q4)
/nascom_ng_fdc/~RAW_READ: U10.12 (~Q), U13.27 (~RAW_READ)
A0_5V: U13.5 (A0); also elsewhere on the board
A1_5V: U13.6 (A1); also elsewhere on the board
CLK1_5V: U13.24 (CLK); also elsewhere on the board
D0_5V: U13.7 (DAL0), U14.3 (D0); also elsewhere on the board
D1_5V: U13.8 (DAL1), U14.4 (D1); also elsewhere on the board
D2_5V: U13.9 (DAL2), U14.6 (D2); also elsewhere on the board
D3_5V: U13.10 (DAL3), U14.11 (D3); also elsewhere on the board
D4_5V: U13.11 (DAL4), U14.13 (D4); also elsewhere on the board
D5_5V: U13.12 (DAL5), U14.14 (D5); also elsewhere on the board
D6_5V: U13.13 (DAL6); also elsewhere on the board
D7_5V: U13.14 (DAL7); also elsewhere on the board
DRIVE_ENABLE: U15.9; also elsewhere on the board
DRQ_5V: U13.38 (DRQ); also elsewhere on the board
GND: C12.2, C15.1, C25.2, D7.2 (A), J5.2, J20.1, J20.3, J20.5, J20.7, J20.9, J20.11, J20.13, J20.15, J20.17, J20.19, J20.21, J20.23, J20.25, J20.27, J20.29, J20.31, J20.33, JP1.1 (A), R20.2, RV1.3, RV2.3, U10.1 (A), U10.6 (Cext), U10.14 (Cext), U11.1 (OEa), U11.8 (GND), U11.15 (OEb), U13.20 (VSS), U14.8 (GND); also elsewhere on the board
INTRQ_5V: U13.39 (INTRQ); also elsewhere on the board
unnamed: C12.1, R16.2, U10.15 (RCext)
unnamed: C15.2, R11.2, U10.7 (RCext)
unnamed: C24.1, D7.1 (K), R20.1
unnamed: C24.2, U13.23 (PUMP)
unnamed: C25.1, U13.26 (VCO)
unnamed: J5.1, U13.1 (ENP)
unnamed: J5.3, U13.29 (TG43)
unnamed: J10.1, U17.11
unnamed: JP1.2 (B), U13.22 (~TEST)
unnamed: RV1.2, U13.33 (WPW)
unnamed: RV2.2, U13.18 (RPW)
unnamed: U13.15 (STEP), U15.11
unnamed: U13.16 (DIRC), U15.5
unnamed: U13.25 (SSO), U15.1
unnamed: U13.30 (WG), U15.3
unnamed: U13.31 (WD), U15.13
unnamed: U14.2 (Q0), U17.1
unnamed: U14.5 (Q1), U17.4
unnamed: U14.7 (Q2), U17.9
unnamed: U14.10 (Q3), U17.12
PORTE4_WR_5V: U14.9 (Cp); also elsewhere on the board
READY: U13.32 (READY); also elsewhere on the board
~DRIVE_READY: J10.3; also elsewhere on the board
~FDC_CS_5V: U13.3 (~CS); also elsewhere on the board
~IO_RESET_5V: U13.19 (~MR), U14.1 (~Mr); also elsewhere on the board
~RD_5V: U13.4 (~RE); also elsewhere on the board
~WR_5V: U13.2 (~WE); also elsewhere on the board

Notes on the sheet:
Out to FDD
Write precompensation No link: always 1-2: never 1-3: for track>43
"L5 (DISK READY)"
(Later VFC versions)
DRIVE PIN 6 PIN 34 Teac FD-55 Drive select 3 READY Pertec FD250 Drive select 3 unused Micropolis 1015 READY Drive select 3 Use "L5 (DISK READY)" to route READY or to select internal READY generation
In from FDD
EPCOS DC film 5mm pitch
Floppy Disk Controller, connector and (most of the) support circuitry.
